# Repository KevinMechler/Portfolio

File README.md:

# Portfolio
A collection of my personal extracurricular projects.

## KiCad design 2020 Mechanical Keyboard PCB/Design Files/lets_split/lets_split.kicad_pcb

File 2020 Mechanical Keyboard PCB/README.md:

# Let's Social Distance

[*Please see original repo*](https://github.com/KevinMechler/Let-s-Social-Distance)

A derivative of the "Let's Split" 40% split ortholinear keyboard originally made by [u/wootpatoot](https://www.reddit.com/user/wootpatoot/).

This was re-designed during my spring break that was extended by the COVID-19 pandemic.
The PCB silkscreen design features artisitic depictions of the coronavirus itself.

New Features:
* Support for a single encoder per PCB in the bottom left or right corner.

    * Optional switch in encoder will be part of the key switch matrix.

* Status LED above the Pro-Micro on each half, controlled by the primary Pro-Micro.

    * Data is carried over TRRS cable

* Minimal silkscreen text 

    * See the layout file for diode locations
    * The stripe of the diode goes towards the square pad.
    
* Removed I2C communication lines

    * To allow for LED data lines to be carried by the TRRS cable

How to Assemble:
* [Let's Split Build Guide](https://github.com/nicinabox/lets-split-guide)

How to Use the Encoders:
* When constructing my keyboard, I decided not to include an encoder.
* Users interested in enabling the encoder should seek examples using the QMK firmware packages.
* The encoder pushbutton pins are connected to imitate a keyboard switch
* EncA is pin 2 and EncB is pin 4 on the Pro Micro.

How to Use the LEDs:
* I decided not to populate the LEDs, though this was designed to accomodate one WS2812B (NeoPixel) RGB LED on either side of each half.
* Since WS2812B LEDs pass-through, a jumper footprint is required to bypass the LEDs on one side and use the others.

Suggestions for future versions:
* Place GND on the TRRS "sleeve" and VCC on the TRRS "tip" to remove potential shorts when a TRS cable is used. This may also require adding a normally-open jumper for the LED data pin on the TRRS connector to allow it to float with the main signal line in the case of a TRS cable.
* Review and improve the LED placement and routing.

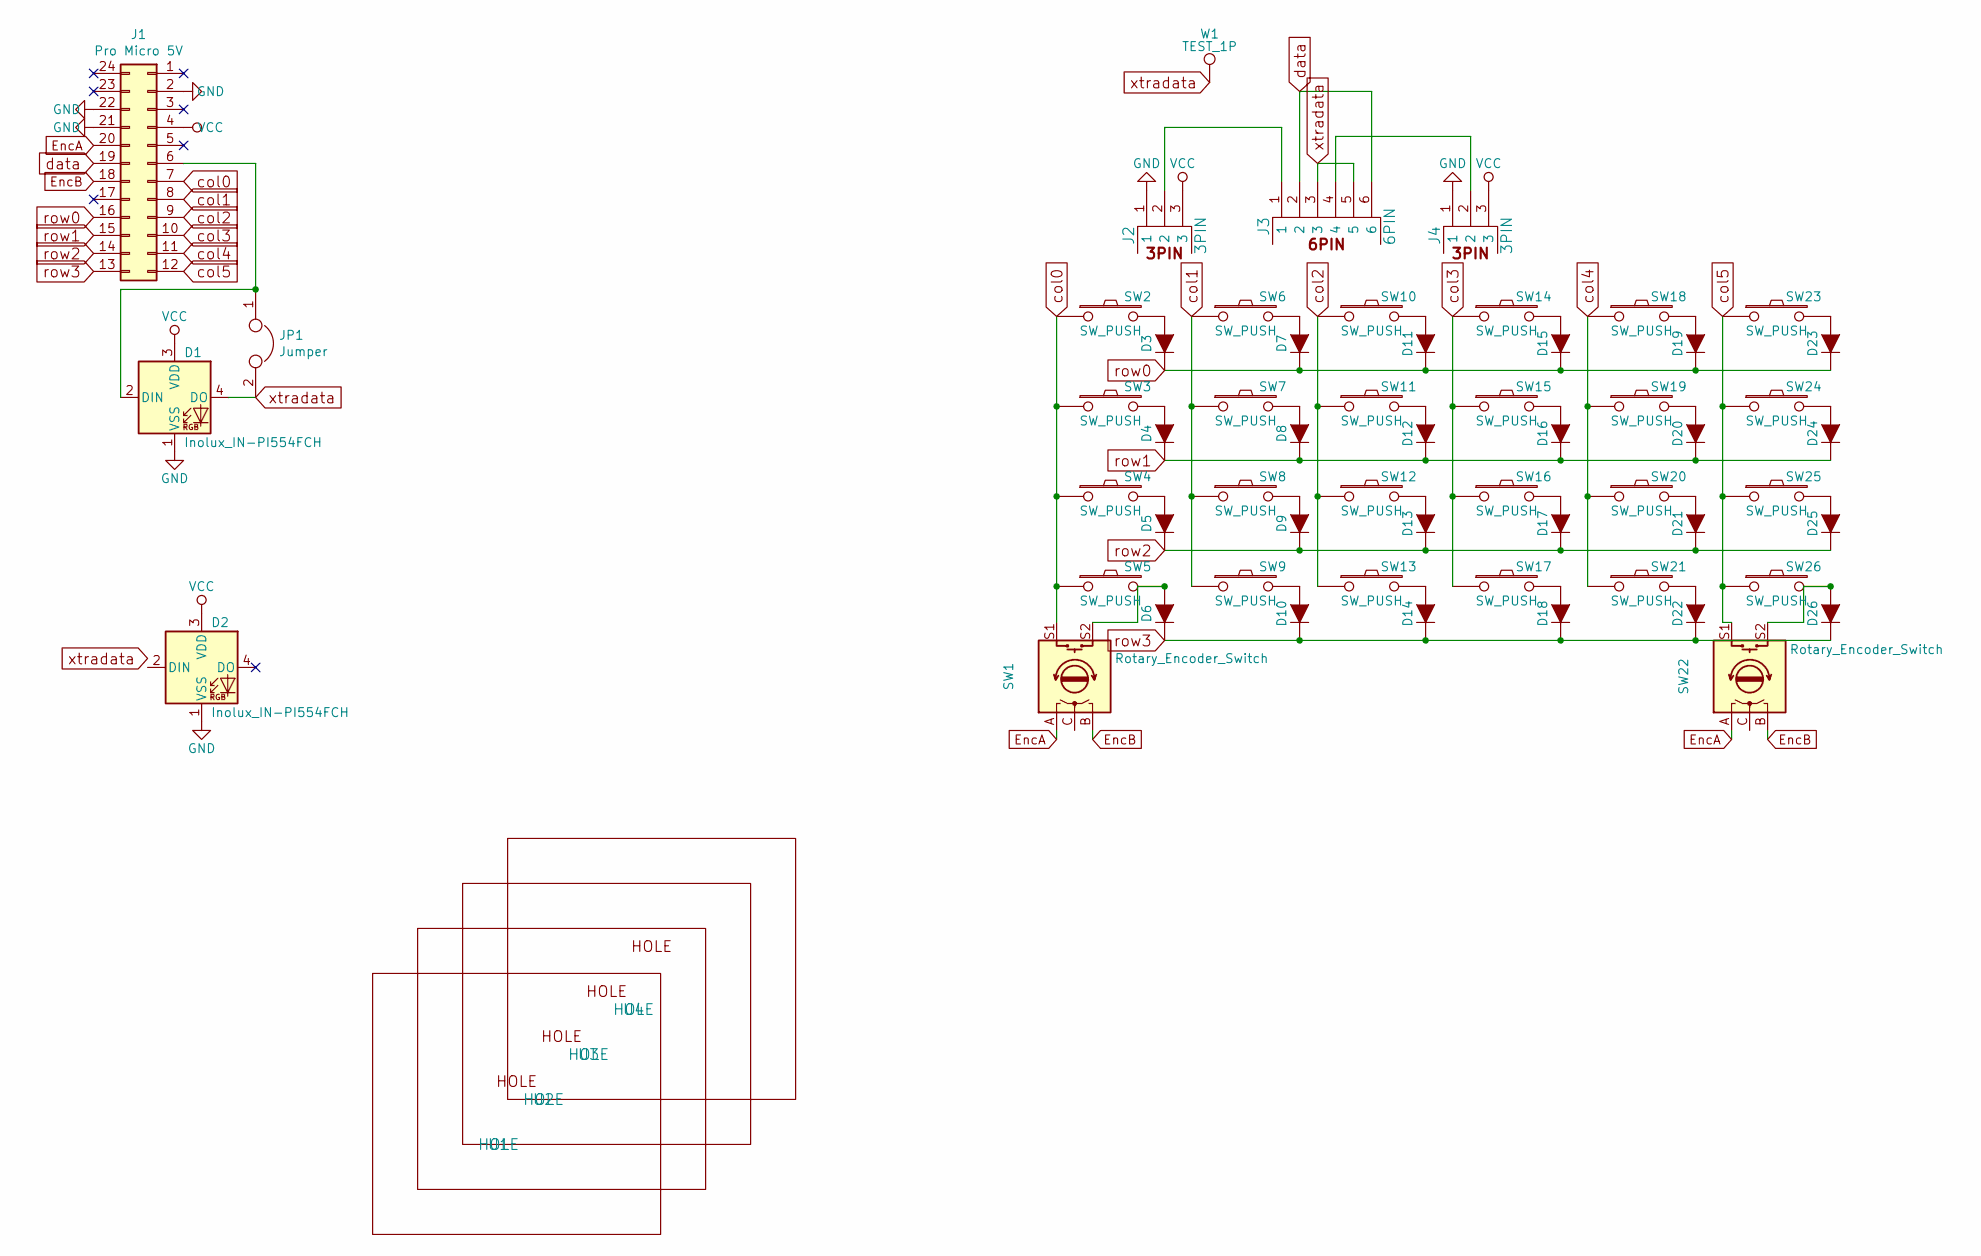
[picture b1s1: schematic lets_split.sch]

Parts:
D1, D2: Inolux_IN-PI554FCH; LED_Inolux_IN-PI554FCH_PLCC4_5.0x5.0mm_P3.2mm; Part Number IN-PI554FCH
D3, D4, D5, D6, D7, D8, D9, D10, D11, D12, D13, D14, D15, D16, D17, D18, D19, D20, D21, D22, D23, D24, D25, D26: D; D_DO-41_SOD81_P10.16mm_Horizontal
J1: Pro Micro 5V; Pro_Micro
J2, J4: 3PIN; 3_pin_TP
J3: 6PIN; 4pin35mmAudio
JP1: Jumper; SolderJumper-2_P1.3mm_Open_TrianglePad1.0x1.5mm
SW1, SW22: Rotary_Encoder_Switch; RotaryEncoder_Alps_EC12E-Switch_Vertical_H20mm
SW2, SW3, SW4, SW5, SW6, SW7, SW8, SW9, SW10, SW11, SW12, SW13, SW14, SW15, SW16, SW17, SW18, SW19, SW20, SW21, SW23, SW24, SW25, SW26: SW_PUSH; MXALPS_FLIP
U1, U2, U3, U4: HOLE; LS_HOLE
W1: TEST_1P; TestPoint_Plated_Hole_D2.0mm

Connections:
EncA: J1.20, SW1.A, SW22.A
EncB: J1.18, SW1.B, SW22.B
GND: D1.1 (VSS), D2.1 (VSS), J1.2, J1.21, J1.22, J2.1, J4.1
unnamed: D1.2 (DIN), J1.6, JP1.1
unnamed: D3.2 (A), SW2.2
unnamed: D4.2 (A), SW3.2
unnamed: D5.2 (A), SW4.2
unnamed: D6.2 (A), SW1.S2, SW5.2
unnamed: D7.2 (A), SW6.2
unnamed: D8.2 (A), SW7.2
unnamed: D9.2 (A), SW8.2
unnamed: D10.2 (A), SW9.2
unnamed: D11.2 (A), SW10.2
unnamed: D12.2 (A), SW11.2
unnamed: D13.2 (A), SW12.2
unnamed: D14.2 (A), SW13.2
unnamed: D15.2 (A), SW14.2
unnamed: D16.2 (A), SW15.2
unnamed: D17.2 (A), SW16.2
unnamed: D18.2 (A), SW17.2
unnamed: D19.2 (A), SW18.2
unnamed: D20.2 (A), SW19.2
unnamed: D21.2 (A), SW20.2
unnamed: D22.2 (A), SW21.2
unnamed: D23.2 (A), SW23.2
unnamed: D24.2 (A), SW24.2
unnamed: D25.2 (A), SW25.2
unnamed: D26.2 (A), SW22.S2, SW26.2
unnamed: J2.2, J3.1
unnamed: J3.4, J4.2
VCC: D1.3 (VDD), D2.3 (VDD), J1.4, J2.3, J4.3
col0: J1.7, SW1.S1, SW2.1, SW3.1, SW4.1, SW5.1
col1: J1.8, SW6.1, SW7.1, SW8.1, SW9.1
col2: J1.9, SW10.1, SW11.1, SW12.1, SW13.1
col3: J1.10, SW14.1, SW15.1, SW16.1, SW17.1
col4: J1.11, SW18.1, SW19.1, SW20.1, SW21.1
col5: J1.12, SW22.S1, SW23.1, SW24.1, SW25.1, SW26.1
data: J1.19, J3.2, J3.6
row0: D3.1 (K), D7.1 (K), D11.1 (K), D15.1 (K), D19.1 (K), D23.1 (K), J1.16
row1: D4.1 (K), D8.1 (K), D12.1 (K), D16.1 (K), D20.1 (K), D24.1 (K), J1.15
row2: D5.1 (K), D9.1 (K), D13.1 (K), D17.1 (K), D21.1 (K), D25.1 (K), J1.14
row3: D6.1 (K), D10.1 (K), D14.1 (K), D18.1 (K), D22.1 (K), D26.1 (K), J1.13
xtradata: D1.4 (DO), J3.3, J3.5, JP1.2, W1.1

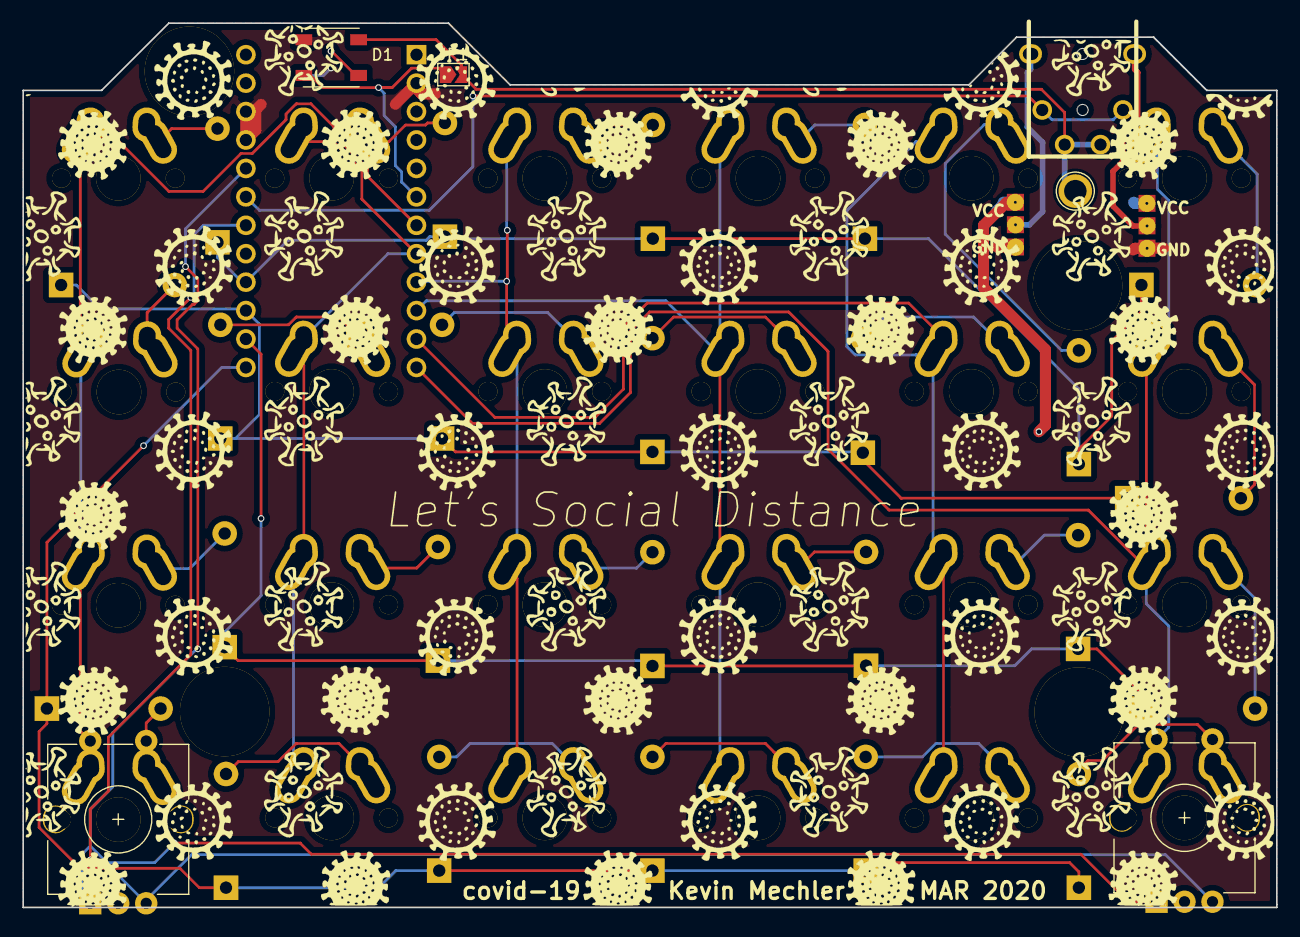
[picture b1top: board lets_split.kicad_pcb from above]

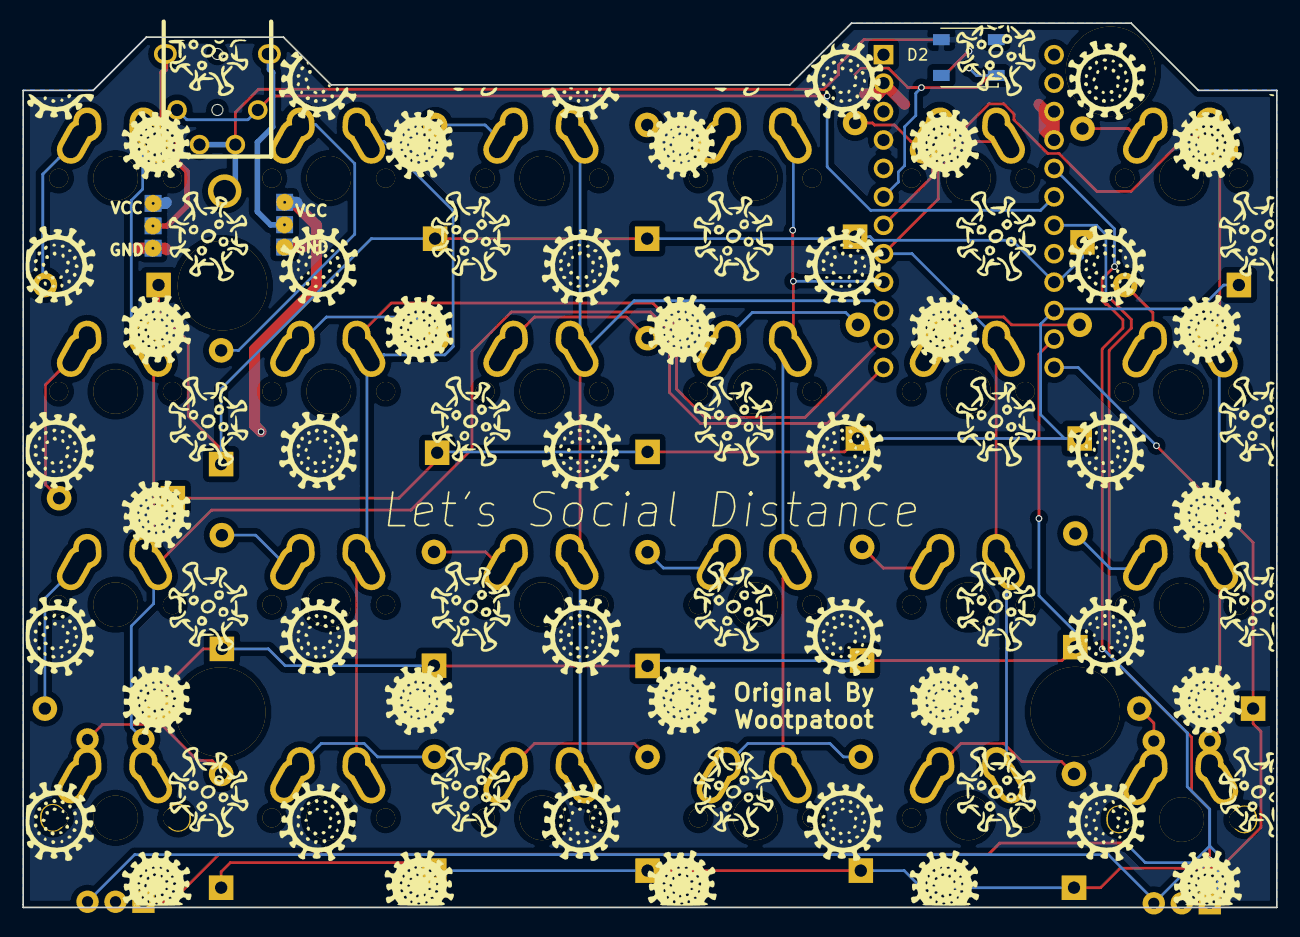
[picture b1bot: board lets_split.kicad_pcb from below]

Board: 2 copper layers, 112.0 x 79.0 mm, 62 parts (2 on the bottom side), 43 nets.

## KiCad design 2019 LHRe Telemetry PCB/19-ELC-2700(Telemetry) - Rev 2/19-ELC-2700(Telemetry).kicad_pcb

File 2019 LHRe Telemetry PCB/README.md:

# 2019 Telemetry PCB
This 2-layer pcb provides a connection between the network of control boards on the vehicle and a BeagleBone Black for logging CAN messages and pushing new firmware to the rest of the control system via CAN bus. Additionally, this device has onboard 12 to 5v switching converter and input protection circuits. A real-time clock and GPS module also allow the BeagleBone to have accurate timestamps on logs and collect GPS data.

1.jpg)

In 2020, we are moving from the BeagleBone to a more powerful Raspberry Pi 4b for faster bootups. To accomodate the requests of other systems on the car for sensors and data aquisition, we are also adding on a separate I2C-based sensor network. Thirdly, long-range radio for transmission of live CAN and I2C messages is being moved onto this board.

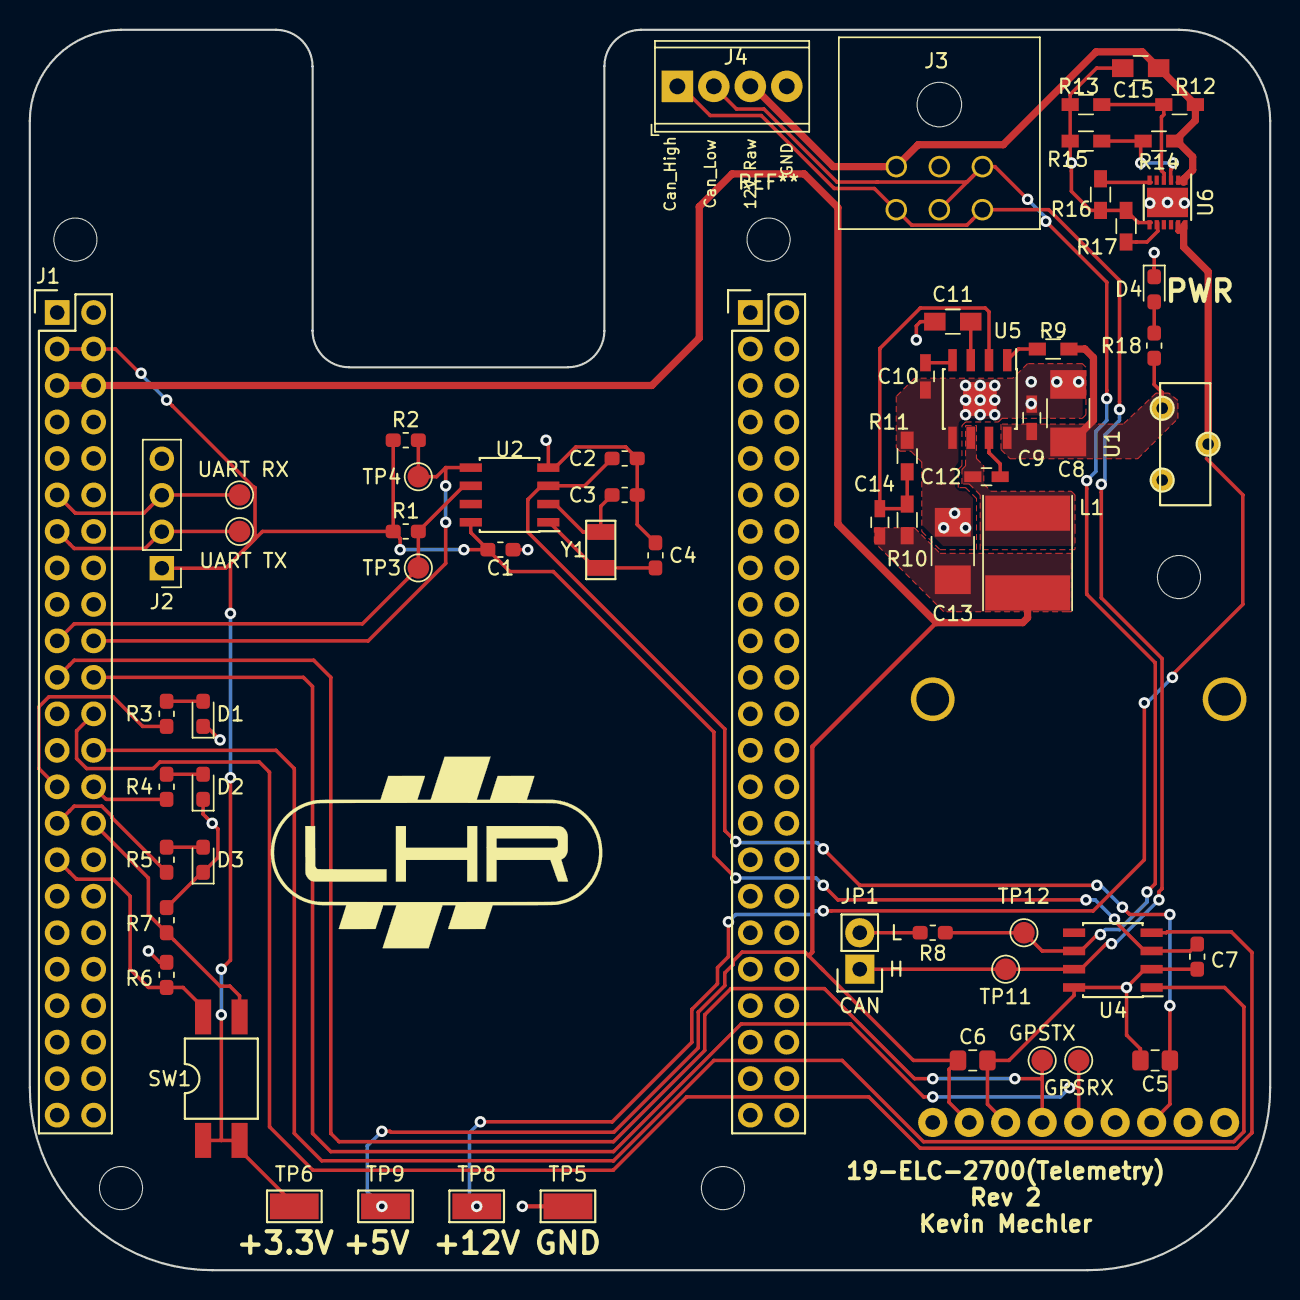
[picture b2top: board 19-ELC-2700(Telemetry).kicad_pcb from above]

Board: 2 copper layers, 86.4 x 86.4 mm, 63 parts (1 on the bottom side), 39 nets.

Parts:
C1, C2, C7: .1 uF; C_0603_1608Metric_Pad1.05x0.95mm_HandSolder
C3, C4: 7 pF; C_0603_1608Metric_Pad1.05x0.95mm_HandSolder
C5: 1 uF; C_0805_2012Metric_Pad1.15x1.40mm_HandSolder
C6: 10 uF; C_0805_2012Metric_Pad1.15x1.40mm_HandSolder
C8, C13: 22uF; C_1210_HandSoldering
C9, C12: 0.1uF; C_0603_HandSoldering
C10: 2.2nF; C_0603_HandSoldering
C11, C15: 1uF; C_0805_HandSoldering
C14: 10pF; C_0603_HandSoldering
D1, D2, D3, D4: LED; LED_0603_1608Metric_Pad1.05x0.95mm_HandSolder
GPSRX: TestPoint; TestPoint_Pad_D1.5mm
GPSTX: TestPoint; TestPoint_Pad_D1.5mm
J1: BeagleBone_Headers; BeagleBone_Black_Headers
J2: Conn_01x04; PinHeader_1x04_P2.54mm_Vertical
J3: 0430450601; Molex_Microfit3_Header_02x03_Angled_43045-060x
J4: 1546215-4; TerminalBlock_Phoenix_MPT-0,5-4-2.54_1x04_P2.54mm_Horizontal
JP1: Jumper; Pin_Header_Straight_1x02_Can_Bus
L1: 4.7uH; L_Taiyo-Yuden_NR-60xx_HandSoldering
R1, R2, R18: 10k; R_0603_1608Metric_Pad1.05x0.95mm_HandSolder
R3, R4, R5: 470; R_0603_1608Metric_Pad1.05x0.95mm_HandSolder
R6, R7: 1k; R_0603_1608Metric_Pad1.05x0.95mm_HandSolder
R8: 120; R_0603_1608Metric_Pad1.05x0.95mm_HandSolder
R9: 10k; R_0603_HandSoldering
R10: 124k; R_0603_HandSoldering
R11: 22.1k; R_0603_HandSoldering
R12, R14: 2.2M; R_0603_HandSoldering
R13: 505k; R_0603_HandSoldering
R15: 226k; R_0603_HandSoldering
R16: 150k; R_0603_HandSoldering
R17: 1.5k; R_0603_HandSoldering
SW1: SW_DIP_x02; 219-2LPST
TP3, TP4, TP11, TP12: TestPoint; TestPoint_Pad_D1.5mm
TP5: GND; TestPoint_Keystone_5015_Micro-Minature
TP6: 3.3V; TestPoint_Keystone_5015_Micro-Minature
TP8: 12V (Protected); TestPoint_Keystone_5015_Micro-Minature
TP9: 5V; TestPoint_Keystone_5015_Micro-Minature
U1: Slide Switch; JS102011CQN
U2: MCP7940N-xSN; SOIC-8_3.9x4.9mm_P1.27mm
U3: Adafruit_Ultimate_GPS_V3
U4: SN65HVD235-Q1; SOIC-8_3.9x4.9mm_P1.27mm
U5: TPS54228DDA; SOIC-8-1EP_3.9x4.9mm_P1.27mm_EP2.35x2.35mm
U6: MAX17608ATC+; DFN-12-1EP_3x3mm_P0.5mm_EP2.05x2.86mm
UART RX: TestPoint; TestPoint_Pad_D1.5mm
UART TX: TestPoint; TestPoint_Pad_D1.5mm
Y1: 32.768 kHz; ECS-.327-12.5-34B-TR

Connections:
+3V3: C1.1, C7.2, J1.P9_3, J1.P9_4, J2.1, R1.1, R2.1, SW1.1, SW1.2, TP6.1, U2.8, U4.3
+5V: C6.1, C13.1, C14.1, J1.P9_5, J1.P9_6, L1.2, R10.1, TP9.1, U3.8
+12V: TP8.1, U1.2, U6.11, U6.12
+BATT: C2.1, C5.1, U2.3, U3.3
/12V to 5V Converter/12V_IN: C8.1, C9.1, R9.2, R18.1, U1.1, U5.8
/12V to 5V Converter/VFB: C14.2, R10.2, R11.1, U5.2
/12V_RAW: C15.1, J3.1, J4.3, R12.1, R14.1, U6.1, U6.2
/CANHigh: J3.4, J3.6, J4.1, JP1.1, TP11.1, U4.7
/CANLow: J3.3, J3.5, J4.2, R8.1, TP12.1, U4.6
/CANRX: J1.P9_24, U4.4
/CANTX: J1.P9_26, U4.1
/GPSRX: GPSRX.1, J1.P9_22, U3.5
/GPSTX: GPSTX.1, J1.P9_21, U3.6
/He Protec/CLMODE: R16.1, U6.6
/He Protec/OVLO: R14.2, R15.1, U6.3
/He Protec/SETI: R17.1, U6.8
/He Protec/UVLO: R12.2, R13.1, U6.4
/I2Cclk: J1.P9_19, R1.2, TP3.1, U2.6
/I2Ccom: J1.P9_20, R2.2, TP4.1, U2.5
/LED0: J1.P9_27, R3.1
/LED1: J1.P9_28, R4.1
/LED2: J1.P9_29, R5.1
/SW1: J1.P9_30, R7.1, SW1.4
/SW2: J1.P9_31, R6.1, SW1.3
/UART_RX: J1.P9_11, J2.3, UART RX.1
/UART_TX: J1.P9_13, J2.2, UART TX.1
GND: C1.2, C2.2, C3.2, C4.2, C5.2, C6.2, C7.1, C8.2, C9.2, C10.2, C11.1, C13.2, C15.2, D1.1, D2.1, D3.1, D4.1, J1.P8_1, J1.P8_2, J1.P9_1, J1.P9_2, J1.P9_43, J1.P9_44, J1.P9_45, J1.P9_46, J2.4, J3.2, J4.4, R6.2, R7.2, R11.2, R13.2, R15.2, R16.2, R17.2, TP5.1, U2.4, U3.7, U4.2, U4.8, U5.5, U5.9, U6.7
unnamed: C3.1, U2.2, Y1.2
unnamed: C4.1, U2.1, Y1.1
unnamed: C10.1, U5.4
unnamed: C11.2, U5.3
unnamed: C12.1, U5.7
unnamed: C12.2, L1.1, U5.6
unnamed: D1.2, R3.2
unnamed: D2.2, R4.2
unnamed: D3.2, R5.2
unnamed: D4.2, R18.2
unnamed: JP1.2, R8.2
unnamed: R9.1, U5.1

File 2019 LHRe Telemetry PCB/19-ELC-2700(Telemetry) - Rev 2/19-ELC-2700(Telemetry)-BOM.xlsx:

Longhorn Racing Electric BOM
Part Number | 19-ELC-2700
Description | Telemetry Rev 2
Refs | Qty | Value | Manufacturer | Part Number | Description | Footprint
C1,C2,C7,C12,C9 | 5 | .1uF |  |  | CAP CER 0.1UF 25V X7R 0603 | 0603 | ?
C10 | 1 | 2.2nF |  |  | CAP CER 2.2NF 25V X7R 0603 | 0603 | ?
C15,C5,C11 | 2 | 1uF |  |  | CAP CER 1UF 25V X7R 0805 | 0805 | ?
C13,C8 | 2 | 22uF |  |  | CAP CER 22UF 16V X7R 1210 | 1210 | ?
C14 | 1 | 10pF |  |  | CAP CER 10PF 25V C0G 0603 | 0603 | ?
C3,C4 | 2 | 7 pF |  |  | CAP CER 7PF 25V X7R 0603 | 0603 | ?
C6 | 1 | 10uF |  |  | CAP CER 10UF 25V X7R 0805 | 0805 | ?
D1,D2,D3 | 3 | LED |  |  | LED RED 0603 | 0603 | ?
D4 | 1 | LED |  |  | LED GREEN 0603 | 0603 | ?
J1 | 1 | BeagleBone_Headers | ? | 2x23 .1" headers (2 of them) | ? | ? | 2x23 .1" headers (2 of them)
J2 | 1 | Conn_01x04 | ? | ? | ? | ? | ?
J3 | 1 | 0430450601 | Molex | 0430450601 | MICROFIT 3.0 CONN HEADER R/A DUAL GOLD 6CKT | 0430450601 | ?
J4 | 1 | 1546215-4 | TE Connectivity | 1546215-4 | TERMI-BLOK PCB MOUNT, 90 4P | ? | ?
JP1 | 1 | Jumper | ? | ? | ? | ? | ?
L1 | 1 | 4.7uH | Taiyo Yuden | NR6028T4R7M | FIXED IND 4.7UH 3A 40.3 MOHM SMD | Nonstandard | ?
R9 | 1 | 10k |  |  | RES SMD 10K OHM 1% 0603 | 0603 | ?
R1,R18,R2 | 3 | 10k |  |  | RES SMD 10K OHM 1% 0603 | 0603 | Might not need to be connected
R10 | 1 | 124k |  |  | RES SMD 124K OHM 1% 0603 | 0603 | ?
R11 | 1 | 22.1k |  |  | RES SMD 22.1K OHM 1% 0603 | 0603 | ?
R12,R14 | 2 | 2.2M |  |  | RES SMD 2.2M OHM 1% 0603 | 0603 | ?
R13 | 1 | 505k |  |  | RES SMD 505K OHM 1% 0603 | 0603 | ?
R15 | 1 | 226k |  |  | RES SMD 226K OHM 1% 0603 | 0603 | ?
R16 | 1 | 150k |  |  | RES SMD 150K OHM 1% 0603 | 0603 | ?
R17 | 1 | 1.5k |  |  | RES SMD 1.5K OHM 1% 0603 | 0603 | ?
R3,R4,R5 | 3 | 470 |  |  | RES SMD 470 OHM 1% 0603 | 0603 | ?
R6,R7 | 2 | 1k |  |  | RES SMD 1K OHM 1% 0603 | 0603 | ?
R8 | 1 | 120 |  |  | RES SMD 120 OHM 1% 0603 | 0603 | ?
SW1 | 1 | SW_DIP_x02 | CTS Electrocomponents | 219-2LPST | SWITCH SLIDE DIP SPST 100MA 20V | 219-2LPST | ?
U1 | 1 | Slide Switch | C&K | JS102011CQN | SWITCH SLIDE SPDT .3A 6VDC | ? | ?
U2 | 1 | MCP7940N-xSN | Microchip | MCP7940N-I/SN | IC RTC CLK/CALENDAR I2C 8-SOIC | 8-Lead SOIC | ?
U3 | 1 | Adafruit_Ultimate_GPS_V3 | Adafruit Industries | 746 | ? | ? | ?
U4 | 1 | SN65HVD235-Q1 | Texas Instruments | SN65HVD235-Q1 | IC CAN TRANSCEIVER 3.3V 8-SOIC | SOIC (8) | ?
U5 | 1 | TPS54228DDA | Texas Instruments | TPS54228DDA | 4.5-V to 18-V Input, 2-A Synchronous Step-Down Converter with Eco-Mode | PowerPad SO-8 | ?
U6 | 1 | MAX17608ATC+ | Maxim Integrated | MAX17608ATC+ | IC 1A OVP/OVC REV PROTECT TDFN | 12-DFN | ?
Y1 | 1 | 32.768 kHz | ECS Inc. | ECS-.327-12.5-34B-TR | CRYSTAL 32.7680KHZ 12.5PF SMD | ? | ?

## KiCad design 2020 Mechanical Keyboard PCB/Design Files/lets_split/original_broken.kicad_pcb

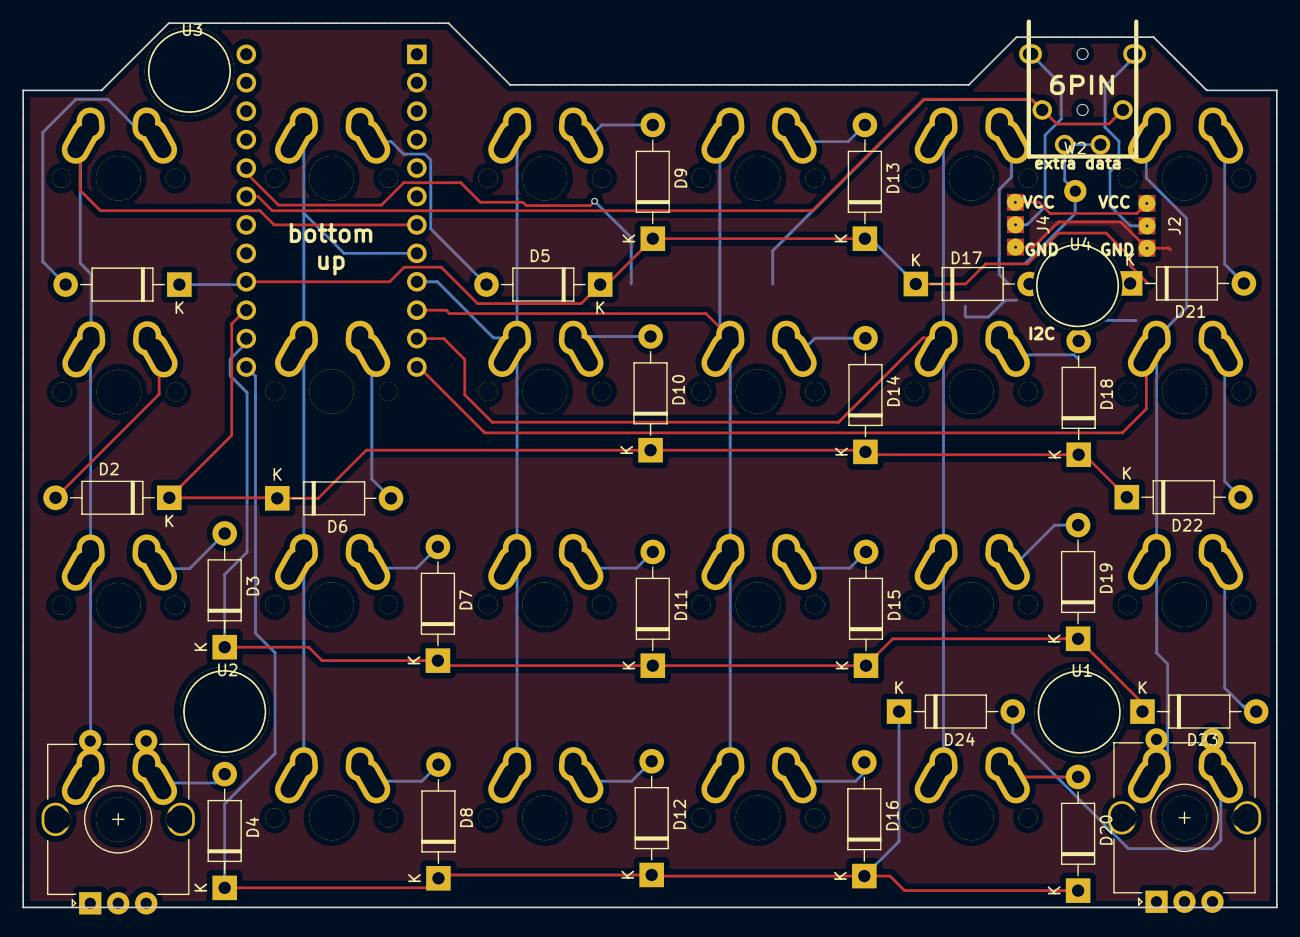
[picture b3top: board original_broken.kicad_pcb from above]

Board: 2 copper layers, 112.0 x 79.0 mm, 59 parts (1 on the bottom side), 42 nets.

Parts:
D1, D2, D3, D4, D5, D6, D7, D8, D9, D10, D11, D12, D13, D14, D15, D16, D17, D18, D19, D20, D21, D22, D23, D24: D; D_DO-41_SOD81_P10.16mm_Horizontal
J2, J4: 3PIN; jumper
J3: 6PIN; 4pin35mmAudio
SW1, SW22: Rotary_Encoder_Switch; RotaryEncoder_Alps_EC12E-Switch_Vertical_H20mm
SW2, SW3, SW4, SW5, SW6, SW7, SW8, SW9, SW10, SW11, SW12, SW13, SW14, SW15, SW16, SW17, SW18, SW19, SW20, SW21, SW23, SW24, SW25, SW26: SW_PUSH; MXALPS_FLIP
U1: TEENSY_2.0
U1#2, U2, U3, U4: HOLE
W2: TEST_1P; SolderWirePad_single_2mmDrill

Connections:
EncA: SW1.A, SW22.A
EncB: SW1.B, SW22.B
GND: J2.1, J4.1, SW1.C, SW22.C, U1.2
unnamed: D1.2, SW2.2
unnamed: D2.2, SW3.2
unnamed: D3.2, SW4.2
unnamed: D4.2, SW1.S2, SW5.2
unnamed: D5.2, SW6.2
unnamed: D6.2, SW7.2
unnamed: D7.2, SW8.2
unnamed: D8.2, SW9.2
unnamed: D9.2, SW10.2
unnamed: D10.2, SW11.2
unnamed: D11.2, SW12.2
unnamed: D12.2, SW13.2
unnamed: D13.2, SW14.2
unnamed: D14.2, SW15.2
unnamed: D15.2, SW16.2
unnamed: D16.2, SW17.2
unnamed: D17.2, SW18.2
unnamed: D18.2, SW19.2
unnamed: D19.2, SW20.2
unnamed: D20.2, SW21.2
unnamed: D21.2, SW23.2
unnamed: D22.2, SW24.2
unnamed: D23.2, SW25.2
unnamed: D24.2, SW22.S2, SW26.2
unnamed: J2.2, J3.1
unnamed: J3.4, J4.2
VCC: J2.3, J4.3, U1.4
col0: SW1.S1, SW2.1, SW3.1, SW4.1, SW5.1, U1.7
col1: SW6.1, SW7.1, SW8.1, SW9.1, U1.8
col2: SW10.1, SW11.1, SW12.1, SW13.1, U1.9
col3: SW14.1, SW15.1, SW16.1, SW17.1, U1.10
col4: SW18.1, SW19.1, SW20.1, SW21.1, U1.11
col5: SW22.S1, SW23.1, SW24.1, SW25.1, SW26.1, U1.12
data: J3.2, J3.6, U1.24
row0: D1.1, D5.1, D9.1, D13.1, D17.1, D21.1, U1.21
row1: D2.1, D6.1, D10.1, D14.1, D18.1, D22.1, U1.20
row2: D3.1, D7.1, D11.1, D15.1, D19.1, D23.1, U1.19
row3: D4.1, D8.1, D12.1, D16.1, D20.1, D24.1, U1.18
xtradata: J3.3, J3.5, W2.1
